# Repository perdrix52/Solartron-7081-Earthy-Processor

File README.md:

# Solartron 7071/7081 Replacement Earthy Processor Board

Sometime around 2020, I acquired a 7071 with a faulty "Brain" or "Earthy Processor" board.
I spent ages trying to fix it and in the end I just gave up on it, until I saw a topic on EEVBLOG started by Lucas Spitzkopf:

[https://www.eevblog.com/forum/repair/solartron-7081-earthy-processor-board-reverse-engineering](https://www.eevblog.com/forum/repair/solartron-7081-earthy-processor-board-reverse-engineering)

describing a two layer replacement PCB he had created for this.

This inspired me to create a four layer replacement board based upon his KiCad schematic, and this is the result.

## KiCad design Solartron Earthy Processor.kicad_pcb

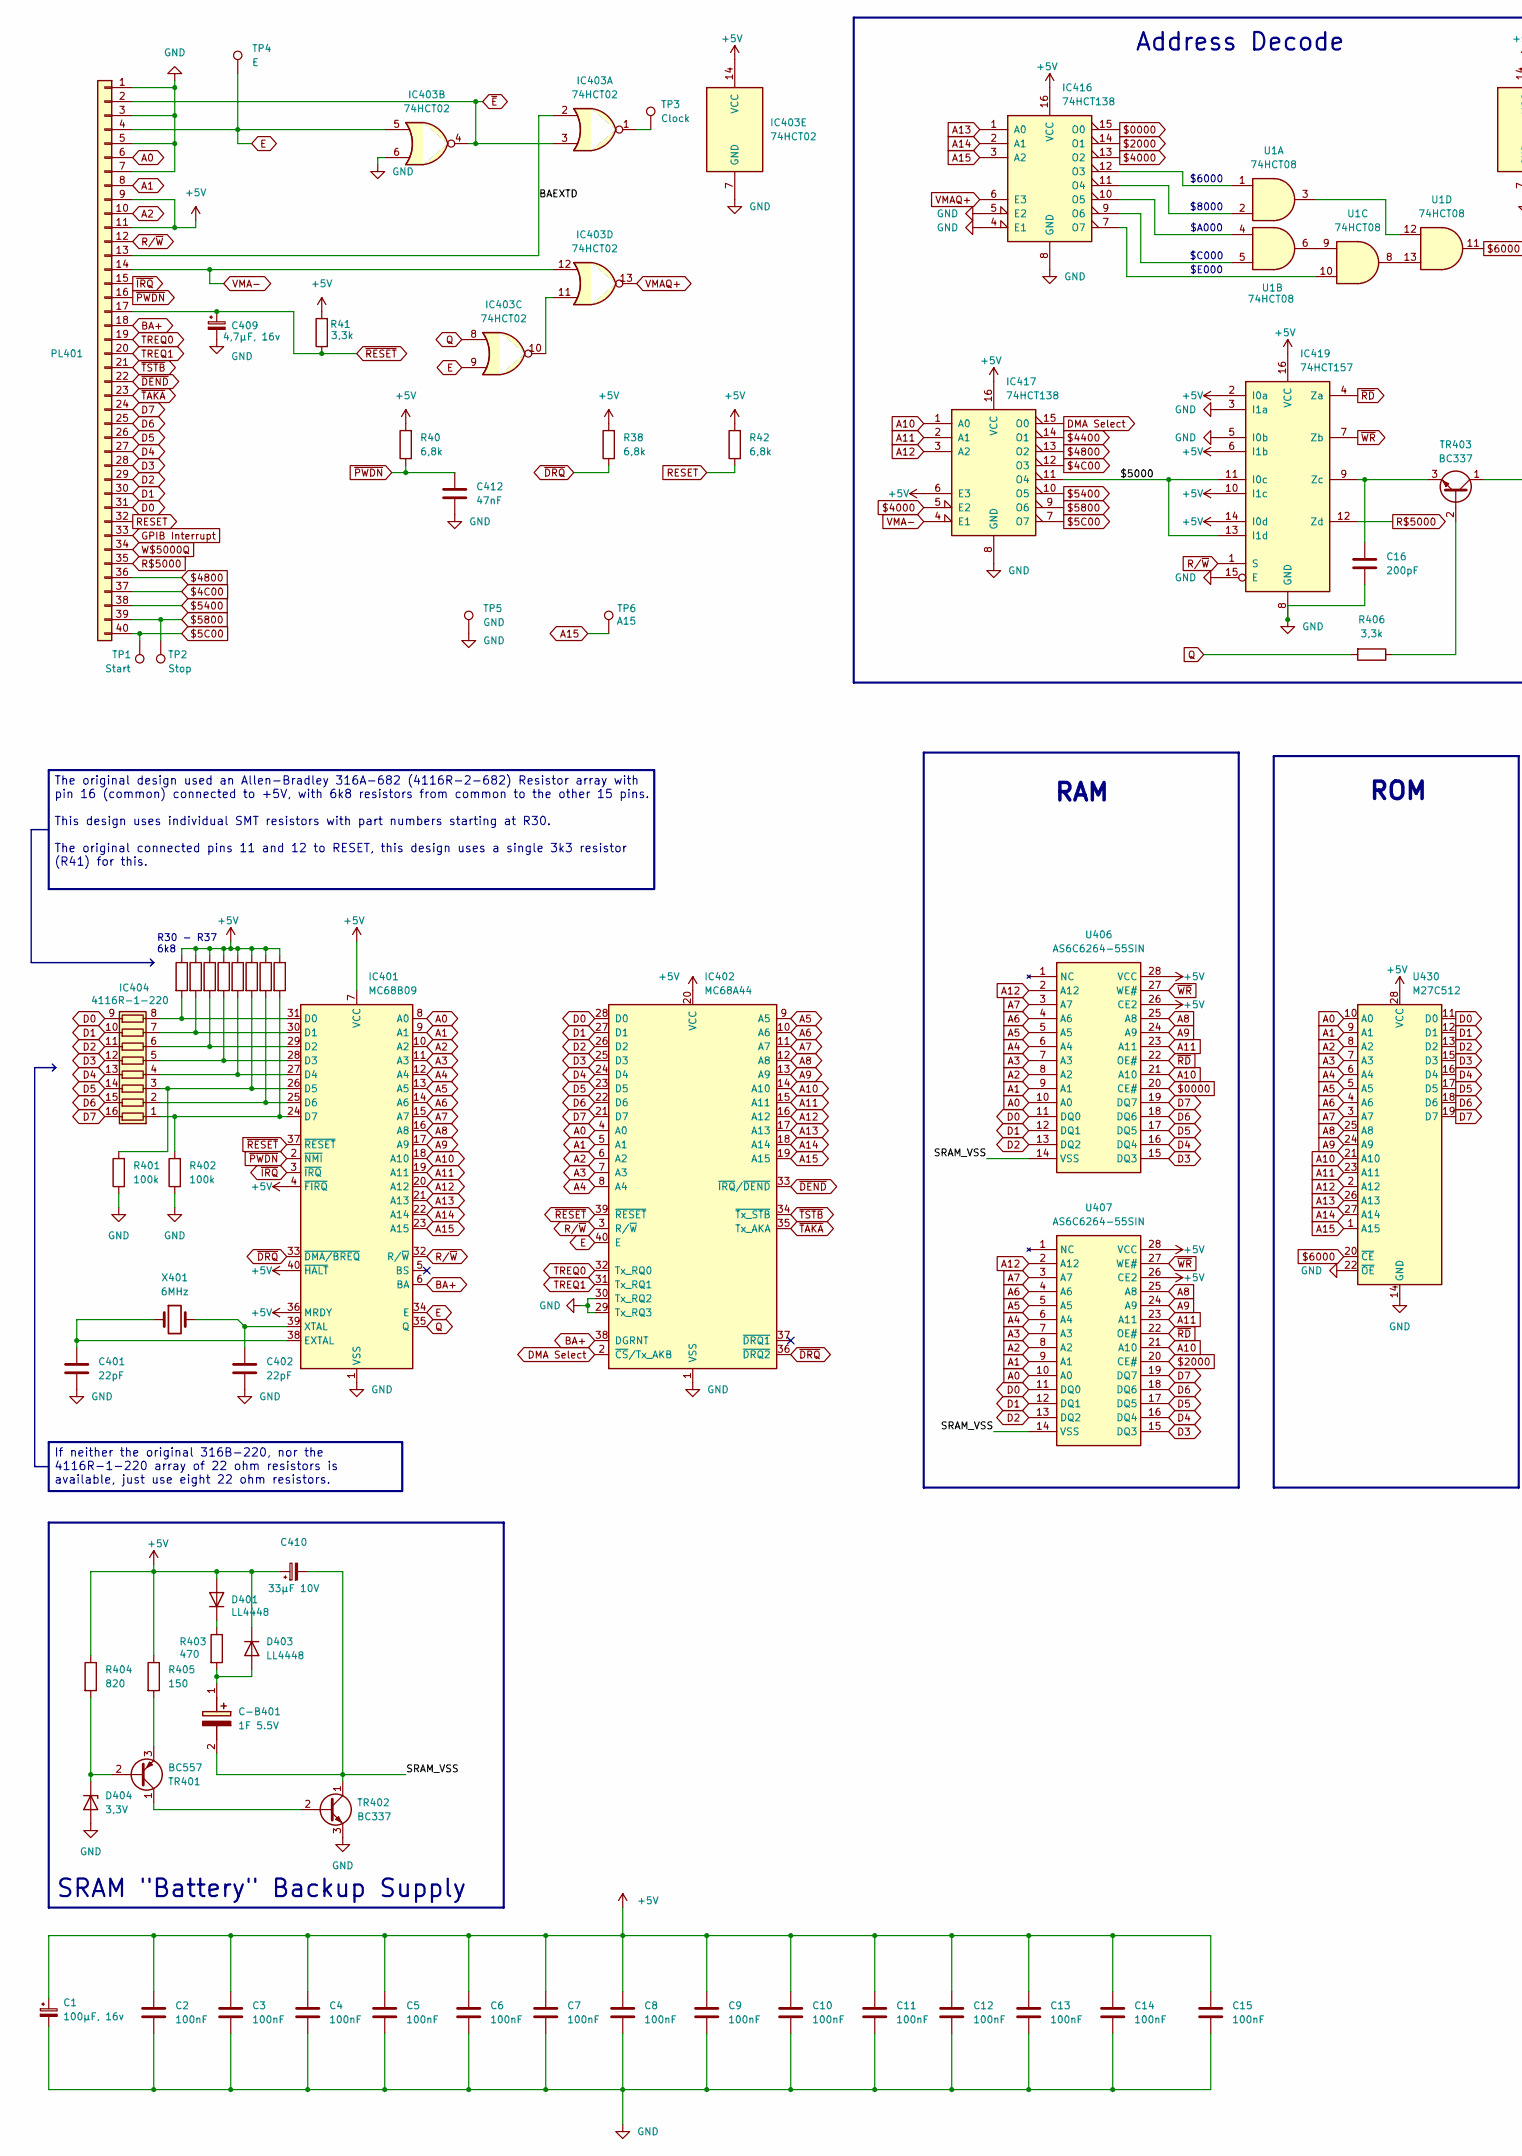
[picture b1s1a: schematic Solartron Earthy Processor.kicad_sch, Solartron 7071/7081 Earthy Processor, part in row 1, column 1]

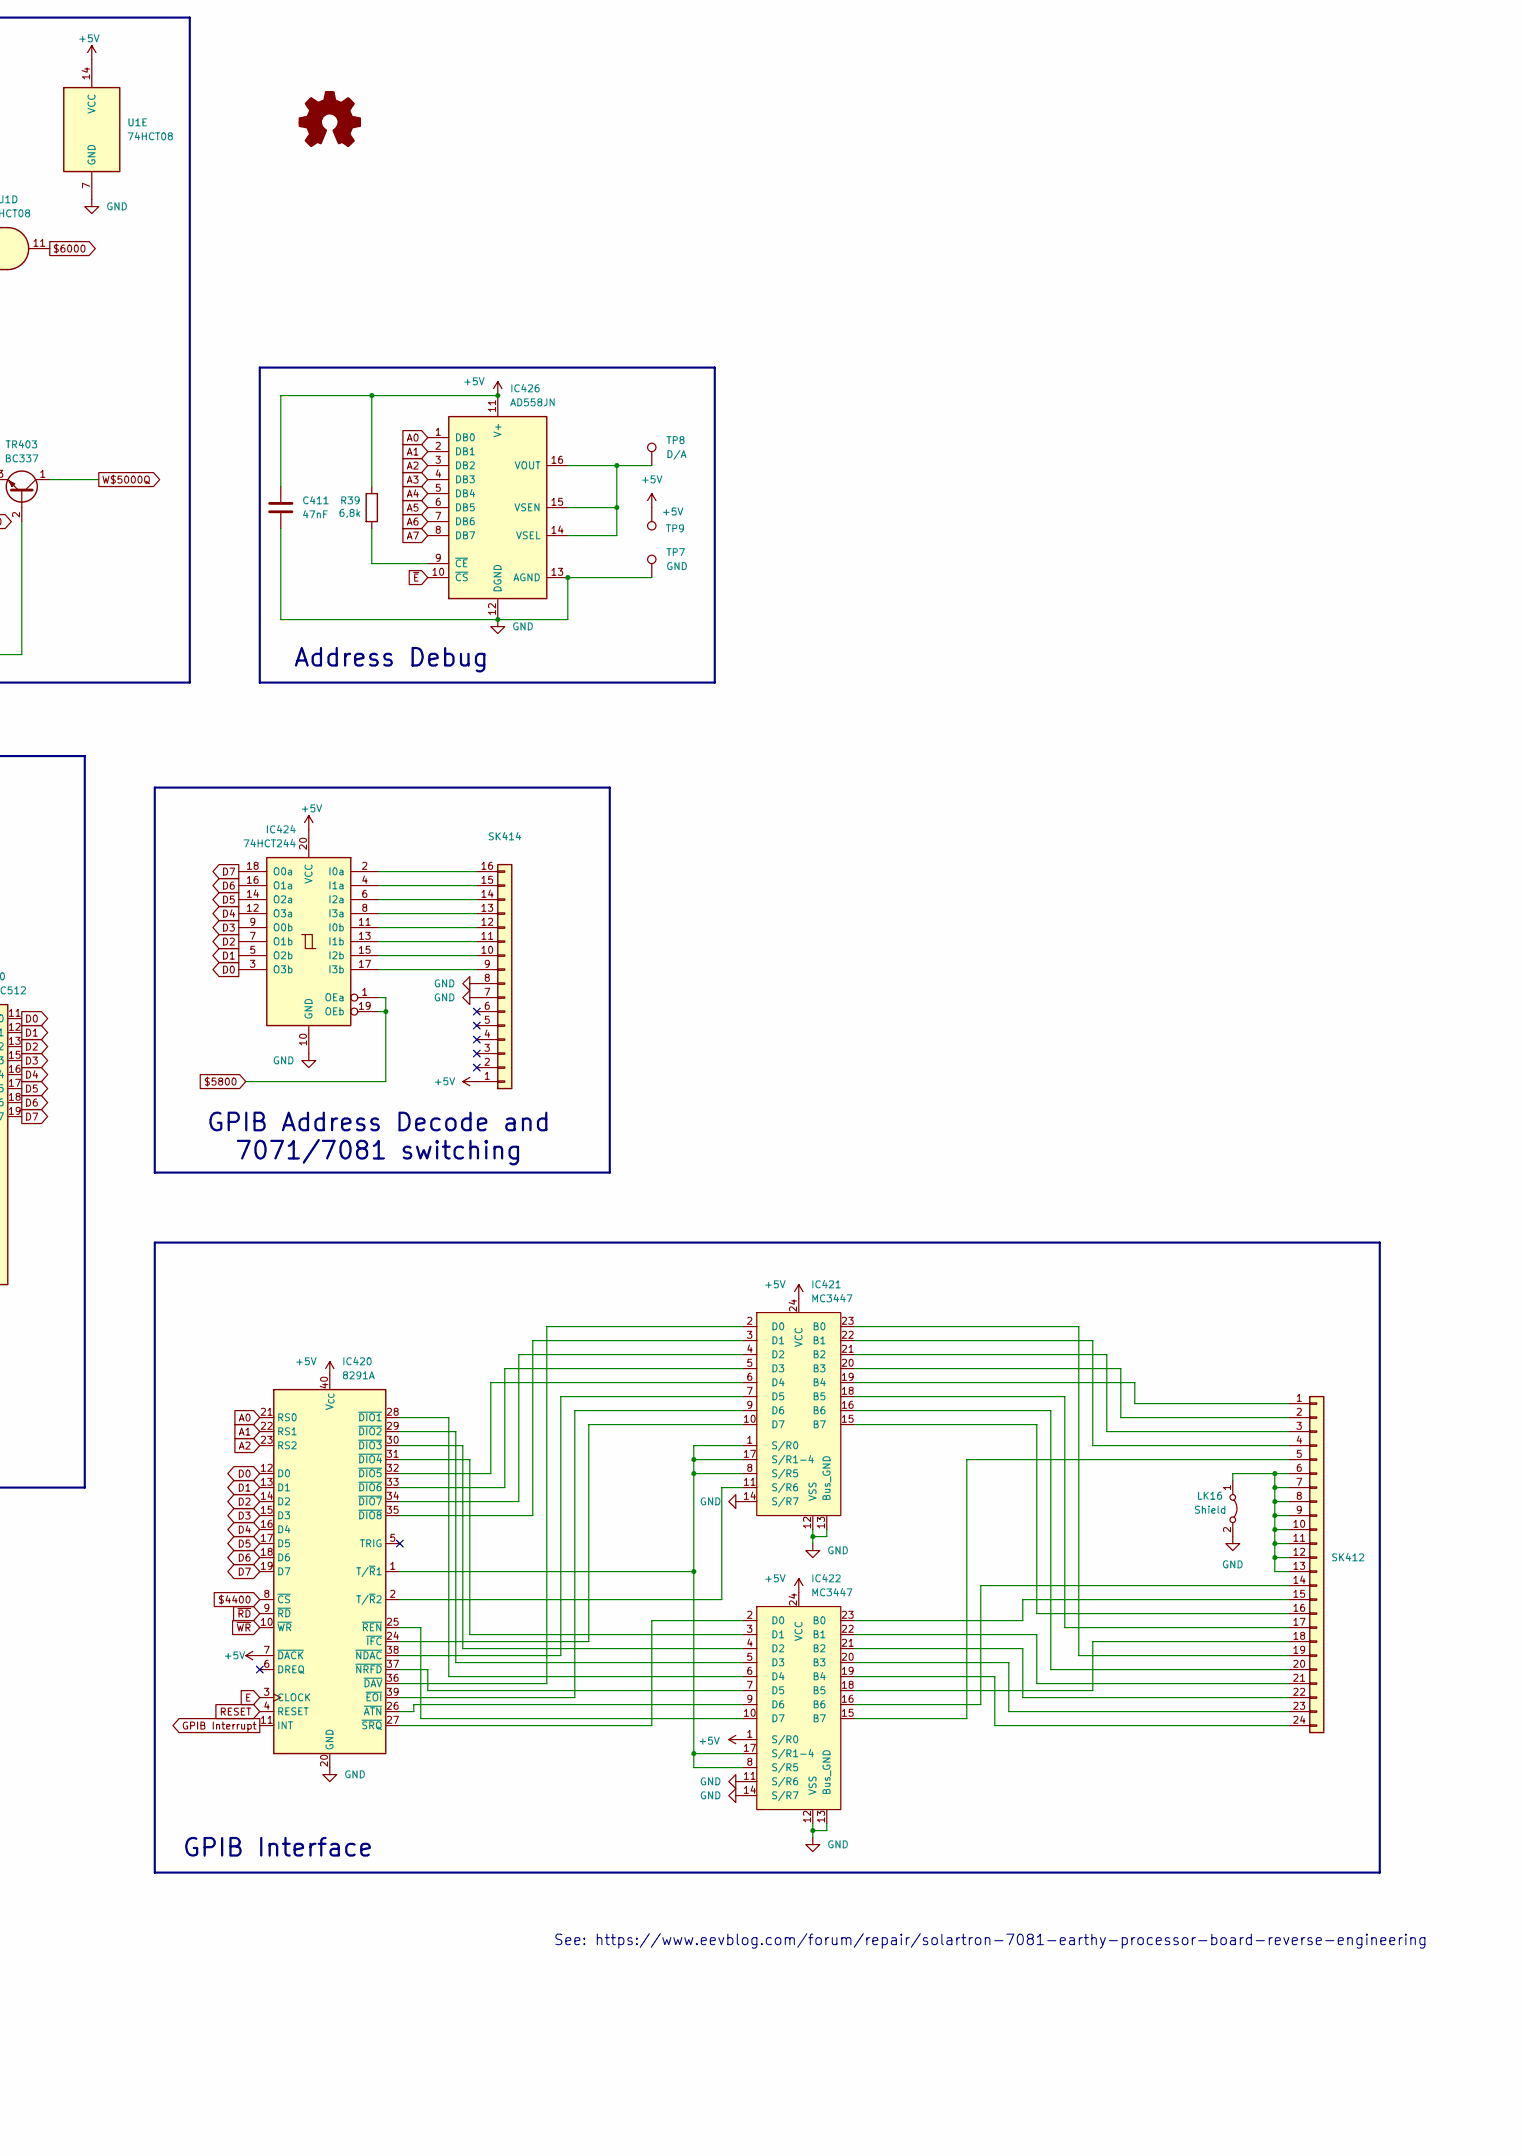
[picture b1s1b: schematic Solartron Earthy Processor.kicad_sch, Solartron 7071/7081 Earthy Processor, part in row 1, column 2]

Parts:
C1: 100µF, 16v; CP_Radial_D10.0mm_P5.00mm
C2, C3, C4, C5, C6, C7, C8, C9, C10, C11, C12, C13, C14, C15: 100nF; C_0805_2012Metric
C16: 200pF; C_0805_2012Metric_Pad1.18x1.45mm_HandSolder
C401, C402: 22pF; C_0805_2012Metric
C409: 4,7µF, 16v; CP_EIA-3216-12_Kemet-S_HandSolder
C410: 33µF 10V; CP_EIA-7343-31_Kemet-D_HandSolder
C411, C412: 47nF; C_0805_2012Metric
C-B401: 1F 5.5V; FGH0H105ZF; Manufacturer_Part_Number FGH0H105ZF; Mouser Part Number 80-FGH0H105ZF
D401, D403: LL4448; D_MiniMELF
D404: 3,3V; D_DO-35_SOD27_P10.16mm_Horizontal
IC401: MC68B09; DIP-40_W15.24mm_Socket_LongPads
IC402: MC68A44; DIP-40_W15.24mm_Socket_LongPads
IC403: 74HCT02; SO-14_3.9x8.65mm_P1.27mm
IC404: 4116R-1-220; DIP-16_W7.62mm_Socket_LongPads
IC416, IC417: 74HCT138; SO-16_3.9x9.9mm_P1.27mm
IC419: 74HCT157; SO-16_3.9x9.9mm_P1.27mm
IC420: 8291A; DIP-40_W15.24mm_Socket_LongPads
IC421, IC422: MC3447; DIP-24_W15.24mm_Socket_LongPads
IC424: 74HCT244; SO-20_12.8x7.5mm_P1.27mm
IC426: AD558JN; DIP-16_W7.62mm_Socket
LK16: Shield; SolderJumper-2_P1.3mm_Open_RoundedPad1.0x1.5mm
PL401: Conn_01x40; IDC-Header_2x20_P2.54mm_Vertical
R30, R31, R32, R33, R34, R35, R36, R37, R38, R39, R40, R42: 6,8k; R_1206_3216Metric
R41, R406: 3,3k; R_1206_3216Metric
R401, R402: 100k; R_1206_3216Metric
R403: 470; R_1206_3216Metric
R404: 820; R_1206_3216Metric
R405: 150; R_1206_3216Metric
SK412: SK412; DIP-24_W15.24mm_Socket_LongPads
SK414: DIP-16_W7.62mm_Socket_LongPads
TP1: Start; TestPoint_Keystone_5000-5004_Miniature
TP2: Stop; TestPoint_Keystone_5000-5004_Miniature
TP3: Clock; TestPoint_Keystone_5000-5004_Miniature
TP4: E; TestPoint_Keystone_5000-5004_Miniature
TP5, TP7: GND; TestPoint_Keystone_5000-5004_Miniature
TP6: A15; TestPoint_Keystone_5000-5004_Miniature
TP8: D/A; TestPoint_Keystone_5000-5004_Miniature
TP9: +5V; TestPoint_Keystone_5000-5004_Miniature
TR401: BC557; TO-92_Inline
TR402, TR403: BC337; TO-92_Inline
U1: 74HCT08; SO-14_3.9x8.65mm_P1.27mm
U406, U407: AS6C6264-55SIN; SOIC127P1181X305-28N; Mouser Part Number 913-AS6C6264-55SIN
U430: M27C512; DIP-28_W15.24mm_Socket_LongPads
X401: 6MHz; Crystal_HC18-U_Horizontal

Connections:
$0000: IC416.15 (O0), U406.20 (CE#)
$4C00: IC417.12 (O3), PL401.37
$5C00: IC417.7 (O7), PL401.40, TP1.1
$2000: IC416.14 (O1), U407.20 (CE#)
$4000: IC416.13 (O2), IC417.5 (E2)
$4400: IC417.14 (O1), IC420.8 (~CS)
$4800: IC417.13 (O2), PL401.36
$5400: IC417.10 (O5), PL401.38
$5800: IC417.9 (O6), IC424.1 (OEa), IC424.19 (OEb), PL401.39, TP2.1
$6000: U1.11, U430.20 (~CE)
+5V: C1.1, C2.1, C3.1, C4.1, C5.1, C6.1, C7.1, C8.1, C9.1, C10.1, C11.1, C12.1, C13.1, C14.1, C15.1, C410.1, C411.1, D401.2 (A), D403.1 (K), IC401.4 (~FIRQ), IC401.7 (VCC), IC401.36 (MRDY), IC401.40 (~HALT), IC402.20 (VCC), IC403.14 (VCC), IC416.16 (VCC), IC417.6 (E3), IC417.16 (VCC), IC419.2 (I0a), IC419.6 (I1b), IC419.10 (I1c), IC419.14 (I0d), IC419.16 (VCC), IC420.7 (~DACK), IC420.40 (V_{CC}), IC421.24 (VCC), IC422.1 (S/R0), IC422.24 (VCC), IC424.20 (VCC), IC426.11 (V+), PL401.9, PL401.11, R30.1, R31.1, R32.1, R33.1, R34.1, R35.1, R36.1, R37.1, R38.2, R39.1, R40.2, R41.2, R42.2, R404.1, R405.1, SK414.1, TP9.1, U1.14 (VCC), U406.26 (CE2), U406.28 (VCC), U407.26 (CE2), U407.28 (VCC), U430.28 (VCC)
/$5000: IC417.11 (O4), IC419.11 (I0c), IC419.13 (I1d)
/BAEXTD: IC403.2, PL401.13
/SRAM_VSS: C410.2, C-B401.2 (-), TR402.1 (C), U406.14 (VSS), U407.14 (VSS)
A0: IC401.8 (A0), IC402.4 (A0), IC420.21 (RS0), IC426.1 (DB0), PL401.6, U406.10 (A0), U407.10 (A0), U430.10 (A0)
A1: IC401.9 (A1), IC402.5 (A1), IC420.22 (RS1), IC426.2 (DB1), PL401.8, U406.9 (A1), U407.9 (A1), U430.9 (A1)
A2: IC401.10 (A2), IC402.6 (A2), IC420.23 (RS2), IC426.3 (DB2), PL401.10, U406.8 (A2), U407.8 (A2), U430.8 (A2)
A3: IC401.11 (A3), IC402.7 (A3), IC426.4 (DB3), U406.7 (A3), U407.7 (A3), U430.7 (A3)
A4: IC401.12 (A4), IC402.8 (A4), IC426.5 (DB4), U406.6 (A4), U407.6 (A4), U430.6 (A4)
A5: IC401.13 (A5), IC402.9 (A5), IC426.6 (DB5), U406.5 (A5), U407.5 (A5), U430.5 (A5)
A6: IC401.14 (A6), IC402.10 (A6), IC426.7 (DB6), U406.4 (A6), U407.4 (A6), U430.4 (A6)
A7: IC401.15 (A7), IC402.11 (A7), IC426.8 (DB7), U406.3 (A7), U407.3 (A7), U430.3 (A7)
A8: IC401.16 (A8), IC402.12 (A8), U406.25 (A8), U407.25 (A8), U430.25 (A8)
A9: IC401.17 (A9), IC402.13 (A9), U406.24 (A9), U407.24 (A9), U430.24 (A9)
A10: IC401.18 (A10), IC402.14 (A10), IC417.1 (A0), U406.21 (A10), U407.21 (A10), U430.21 (A10)
A11: IC401.19 (A11), IC402.15 (A11), IC417.2 (A1), U406.23 (A11), U407.23 (A11), U430.23 (A11)
A12: IC401.20 (A12), IC402.16 (A12), IC417.3 (A2), U406.2 (A12), U407.2 (A12), U430.2 (A12)
A13: IC401.21 (A13), IC402.17 (A13), IC416.1 (A0), U430.26 (A13)
A14: IC401.22 (A14), IC402.18 (A14), IC416.2 (A1), U430.27 (A14)
A15: IC401.23 (A15), IC402.19 (A15), IC416.3 (A2), TP6.1, U430.1 (A15)
BA+: IC401.6 (BA), IC402.38 (DGRNT), PL401.18
D0: IC402.28 (D0), IC404.9 (R8.2), IC420.12 (D0), IC424.3 (O3b), PL401.31, U406.11 (DQ0), U407.11 (DQ0), U430.11 (D0)
D1: IC402.27 (D1), IC404.10 (R7.2), IC420.13 (D1), IC424.5 (O2b), PL401.30, U406.12 (DQ1), U407.12 (DQ1), U430.12 (D1)
D2: IC402.26 (D2), IC404.11 (R6.2), IC420.14 (D2), IC424.7 (O1b), PL401.29, U406.13 (DQ2), U407.13 (DQ2), U430.13 (D2)
D3: IC402.25 (D3), IC404.12 (R5.2), IC420.15 (D3), IC424.9 (O0b), PL401.28, U406.15 (DQ3), U407.15 (DQ3), U430.15 (D3)
D4: IC402.24 (D4), IC404.13 (R4.2), IC420.16 (D4), IC424.12 (O3a), PL401.27, U406.16 (DQ4), U407.16 (DQ4), U430.16 (D4)
D5: IC402.23 (D5), IC404.14 (R3.2), IC420.17 (D5), IC424.14 (O2a), PL401.26, U406.17 (DQ5), U407.17 (DQ5), U430.17 (D5)
D6: IC402.22 (D6), IC404.15 (R2.2), IC420.18 (D6), IC424.16 (O1a), PL401.25, U406.18 (DQ6), U407.18 (DQ6), U430.18 (D6)
D7: IC402.21 (D7), IC404.16 (R1.2), IC420.19 (D7), IC424.18 (O0a), PL401.24, U406.19 (DQ7), U407.19 (DQ7), U430.19 (D7)
DMA Select: IC402.2 (~CS/Tx_AKB), IC417.15 (O0)
E: IC401.34 (E), IC402.40 (E), IC403.5, IC403.9, IC420.3 (CLOCK), PL401.4, TP4.1
GND: C1.2, C2.2, C3.2, C4.2, C5.2, C6.2, C7.2, C8.2, C9.2, C10.2, C11.2, C12.2, C13.2, C14.2, C15.2, C16.2, C401.2, C402.2, C409.2, C411.2, C412.2, D404.2 (A), IC401.1 (VSS), IC402.1 (VSS), IC402.29 (Tx_RQ3), IC402.30 (Tx_RQ2), IC403.6, IC403.7 (GND), IC416.4 (E1), IC416.5 (E2), IC416.8 (GND), IC417.8 (GND), IC419.3 (I1a), IC419.5 (I0b), IC419.8 (GND), IC419.15 (E), IC420.20 (GND), IC421.12 (VSS), IC421.13 (Bus_GND), IC421.14 (S/R7), IC422.11 (S/R6), IC422.12 (VSS), IC422.13 (Bus_GND), IC422.14 (S/R7), IC424.10 (GND), IC426.12 (DGND), IC426.13 (AGND), LK16.2 (B), PL401.1, PL401.3, PL401.5, PL401.7, R401.1, R402.1, SK414.7, SK414.8, TP5.1, TP7.1, TR402.3 (E), U1.7 (GND), U430.14 (GND), U430.22 (~OE)
GPIB Interrupt: IC420.11 (INT), PL401.33
unnamed: C-B401.1 (+), D403.2 (A), R403.2
unnamed: D401.1 (K), R403.1
unnamed: D404.1 (K), R404.2, TR401.2 (B)
unnamed: IC401.31 (D0), IC404.8 (R8.1), R30.2
unnamed: IC401.30 (D1), IC404.7 (R7.1), R31.2
unnamed: IC401.29 (D2), IC404.6 (R6.1), R32.2
unnamed: IC401.28 (D3), IC404.5 (R5.1), R33.2
unnamed: IC401.27 (D4), IC404.4 (R4.1), R34.2
unnamed: IC401.26 (D5), IC404.3 (R3.1), R35.2, R401.2
unnamed: IC401.25 (D6), IC404.2 (R2.1), R36.2
unnamed: IC401.24 (D7), IC404.1 (R1.1), R37.2, R402.2
unnamed: C401.1, IC401.38 (EXTAL), X401.1
unnamed: C402.1, IC401.39 (XTAL), X401.2
unnamed: IC403.1, TP3.1
unnamed: IC403.10, IC403.11
unnamed: IC416.12 (O3), U1.1
unnamed: IC416.11 (O4), U1.2
unnamed: IC416.10 (O5), U1.4
unnamed: IC416.9 (O6), U1.5
unnamed: IC416.7 (O7), U1.10
unnamed: C16.1, IC419.9 (Zc), TR403.3 (E)
unnamed: IC420.1 (T/~R1), IC421.1 (S/R0), IC421.8 (S/R5), IC421.17 (S/R1-4), IC422.8 (S/R5), IC422.17 (S/R1-4)
unnamed: IC420.2 (T/~R2), IC421.11 (S/R6)
unnamed: IC420.26 (~ATN), IC422.9 (D6)
unnamed: IC420.36 (~DAV), IC421.2 (D0)
unnamed: IC420.28 (~DIO1), IC422.6 (D4)
unnamed: IC420.29 (~DIO2), IC422.5 (D3)
unnamed: IC420.30 (~DIO3), IC422.4 (D2)
unnamed: IC420.31 (~DIO4), IC422.3 (D1)
unnamed: IC420.32 (~DIO5), IC421.6 (D4)
unnamed: IC420.33 (~DIO6), IC421.5 (D3)
unnamed: IC420.34 (~DIO7), IC421.4 (D2)
unnamed: IC420.35 (~DIO8), IC421.3 (D1)
unnamed: IC420.39 (~EOI), IC421.9 (D6)
unnamed: IC420.24 (~IFC), IC421.10 (D7)
unnamed: IC420.38 (~NDAC), IC421.7 (D5)
unnamed: IC420.37 (~NRFD), IC422.7 (D5)
unnamed: IC420.25 (~REN), IC422.10 (D7)
unnamed: IC420.27 (~SRQ), IC422.2 (D0)
unnamed: IC421.23 (B0), SK412.19
unnamed: IC421.22 (B1), SK412.4
unnamed: IC421.21 (B2), SK412.3
unnamed: IC421.20 (B3), SK412.2
unnamed: IC421.19 (B4), SK412.1
unnamed: IC421.18 (B5), SK412.17
unnamed: IC421.16 (B6), SK412.20
unnamed: IC421.15 (B7), SK412.16
unnamed: IC422.23 (B0), SK412.15
unnamed: IC422.22 (B1), SK412.21
unnamed: IC422.21 (B2), SK412.22
unnamed: IC422.20 (B3), SK412.23
unnamed: IC422.19 (B4), SK412.24
unnamed: IC422.18 (B5), SK412.18
unnamed: IC422.16 (B6), SK412.14
unnamed: IC422.15 (B7), SK412.5
unnamed: IC424.2 (I0a), SK414.16
unnamed: IC424.11 (I0b), SK414.12
unnamed: IC424.4 (I1a), SK414.15
unnamed: IC424.13 (I1b), SK414.11
unnamed: IC424.6 (I2a), SK414.14
unnamed: IC424.15 (I2b), SK414.10
unnamed: IC424.8 (I3a), SK414.13
unnamed: IC424.17 (I3b), SK414.9
unnamed: IC426.14 (VSEL), IC426.15 (VSEN), IC426.16 (VOUT), TP8.1
unnamed: IC426.9 (~CE), R39.2
unnamed: LK16.1 (A), SK412.6, SK412.7, SK412.8, SK412.9, SK412.10, SK412.11, SK412.12, SK412.13
unnamed: TR401.1 (C), TR402.2 (B)
unnamed: R405.2, TR401.3 (E)
unnamed: R406.1, TR403.2 (B)
unnamed: U1.6, U1.9
unnamed: U1.3, U1.12
unnamed: U1.8, U1.13
Q: IC401.35 (Q), IC403.8, R406.2
R$5000: IC419.12 (Zd), PL401.35
RESET: IC420.4 (RESET), PL401.32, R42.1
R/~W: IC401.32 (R/~W), IC402.3 (R/~W), IC419.1 (S), PL401.12
TREQ0: IC402.32 (Tx_RQ0), PL401.19
TREQ1: IC402.31 (Tx_RQ1), PL401.20
VMA-: IC403.12, IC417.4 (E1), PL401.14
VMAQ+: IC403.13, IC416.6 (E3)
W$5000Q: PL401.34, TR403.1 (C)
~DEND: IC402.33 (~IRQ/~DEND), PL401.22
~DRQ: IC401.33 (~DMA/BREQ), IC402.36 (~DRQ2), R38.1
~E: IC403.3, IC403.4, IC426.10 (~CS), PL401.2
~IRQ: IC401.3 (~IRQ), PL401.15
~PWDN: C412.1, IC401.2 (~NMI), PL401.16, R40.1
~RD: IC419.4 (Za), IC420.9 (~RD), U406.22 (OE#), U407.22 (OE#)
~RESET: C409.1, IC401.37 (~RESET), IC402.39 (~RESET), PL401.17, R41.1
~TAKA: IC402.35 (Tx_AKA), PL401.23
~TSTB: IC402.34 (~Tx_STB), PL401.21
~WR: IC419.7 (Zb), IC420.10 (~WR), U406.27 (WE#), U407.27 (WE#)

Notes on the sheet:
Address Debug
See: https://www.eevblog.com/forum/repair/solartron-7081-earthy-processor-board-reverse-engineering
SRAM "Battery" Backup Supply
R30 - R37 6k8
ROM
$8000
$E000
$A000
GPIB Address Decode and 7071/7081 switching
Address Decode
$C000
$6000
GPIB Interface
RAM
The original design used an Allen-Bradley 316A-682 (4116R-2-682) Resistor array with pin 16 (common) connected to +5V, with 6k8 resistors from common to the other 15 pins. This design uses individual SMT resistors with part numbers starting at R30. The original connected pins 11 and 12 to RESET, th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
If neither the original 316B-220, nor the 4116R-1-220 array of 22 ohm resistors is available, just use eight 22 ohm resistors.

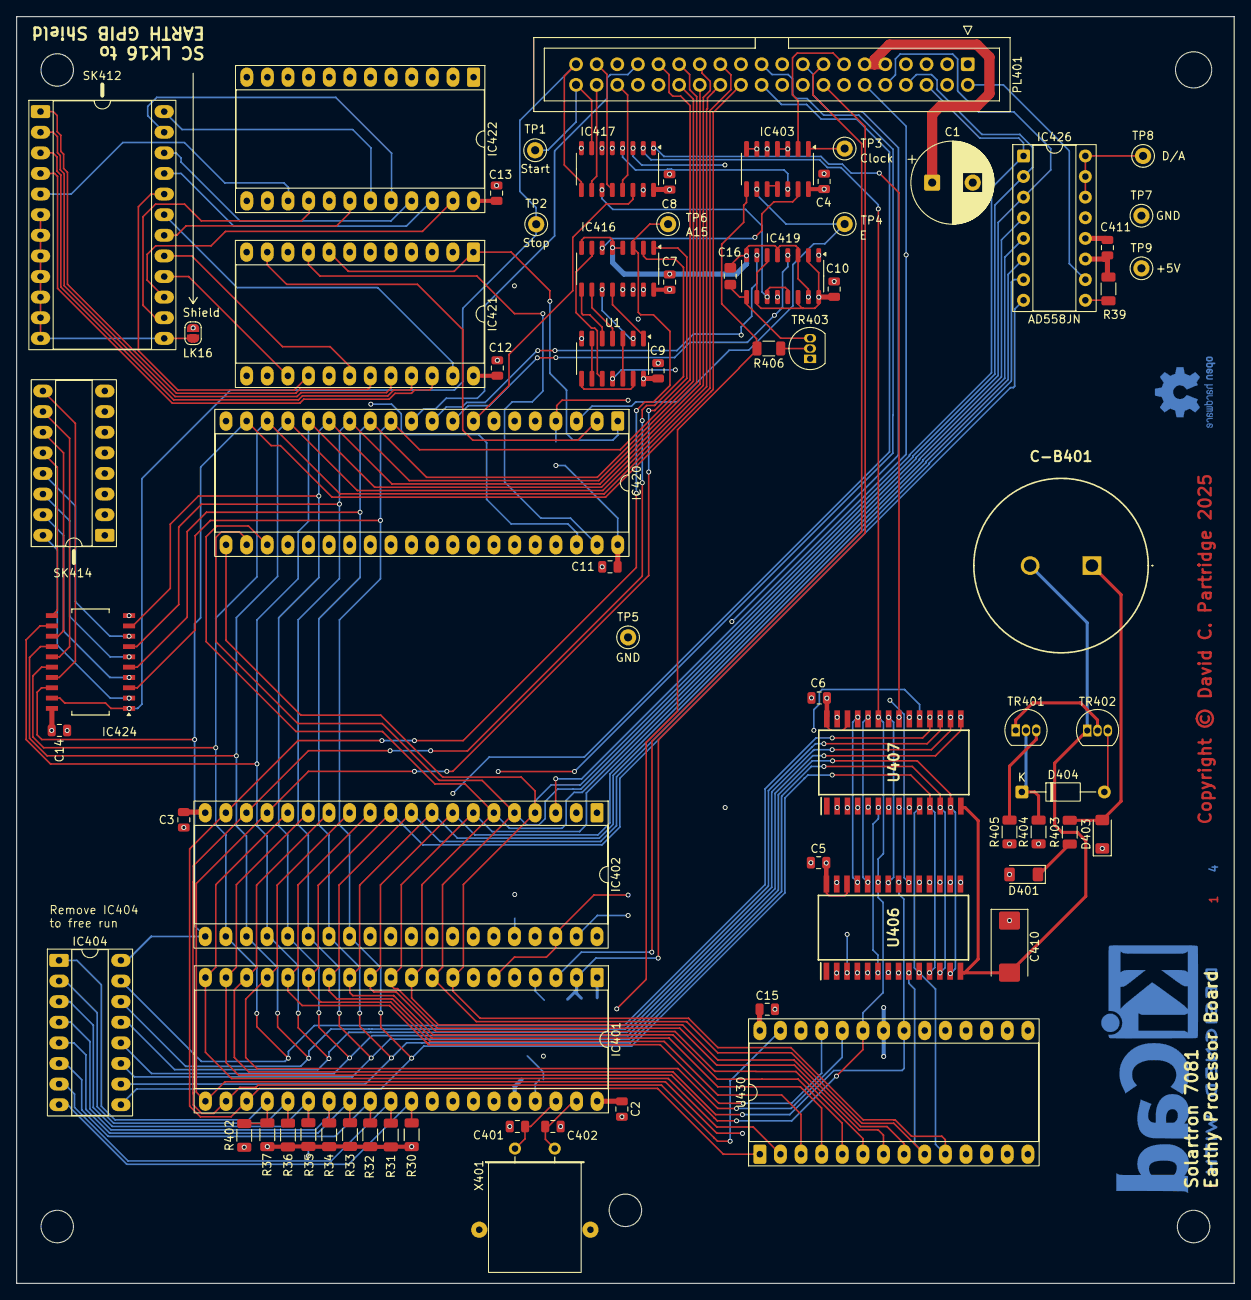
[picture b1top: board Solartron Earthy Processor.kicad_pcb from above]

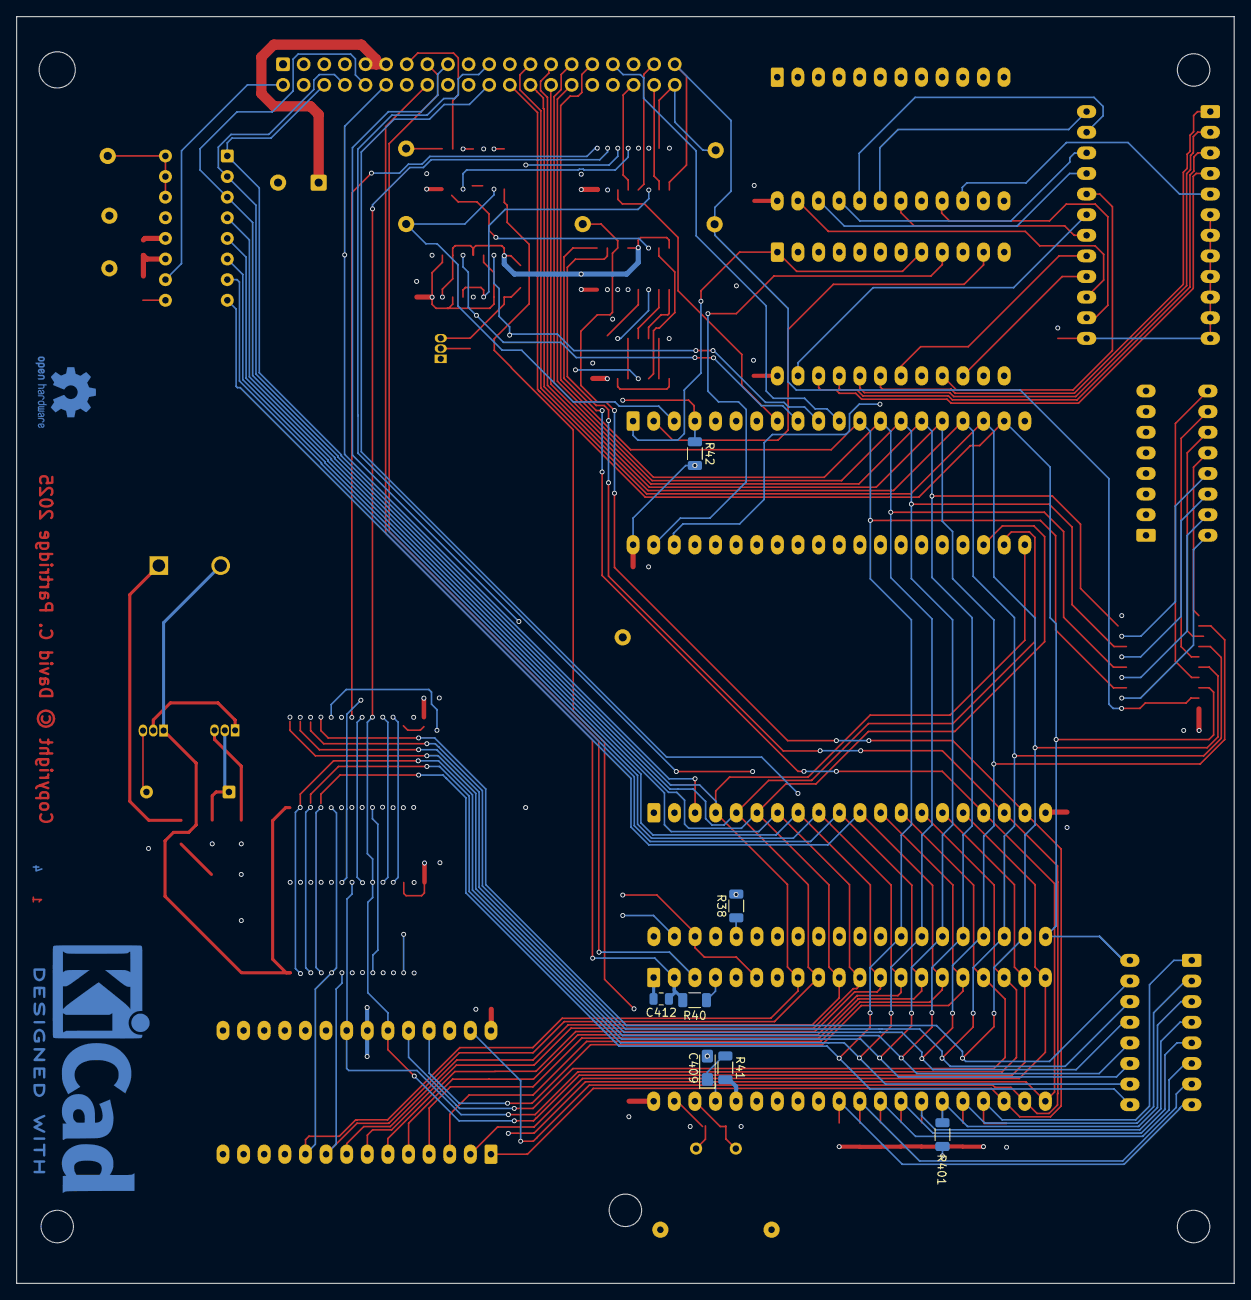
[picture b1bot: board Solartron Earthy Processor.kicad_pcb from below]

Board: 4 copper layers, 150.0 x 156.1 mm, 80 parts (8 on the bottom side), 134 nets.

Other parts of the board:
Kicad_Logo: KiCad-Logo2_12mm_Copper
LayerMarker: LayerMarker_4_6.35x2.54mm_TextH1mm_P1.27mm

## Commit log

2025-09-16 Add license

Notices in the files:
Solartron Earthy Processor.kicad_pcb:
Copyright © David C. Partridge 2025
Solartron Earthy Processor.kicad_sch:
Copyright © David C. Partridge 2025 [david.partridge@perdrix.co.uk], based upon
